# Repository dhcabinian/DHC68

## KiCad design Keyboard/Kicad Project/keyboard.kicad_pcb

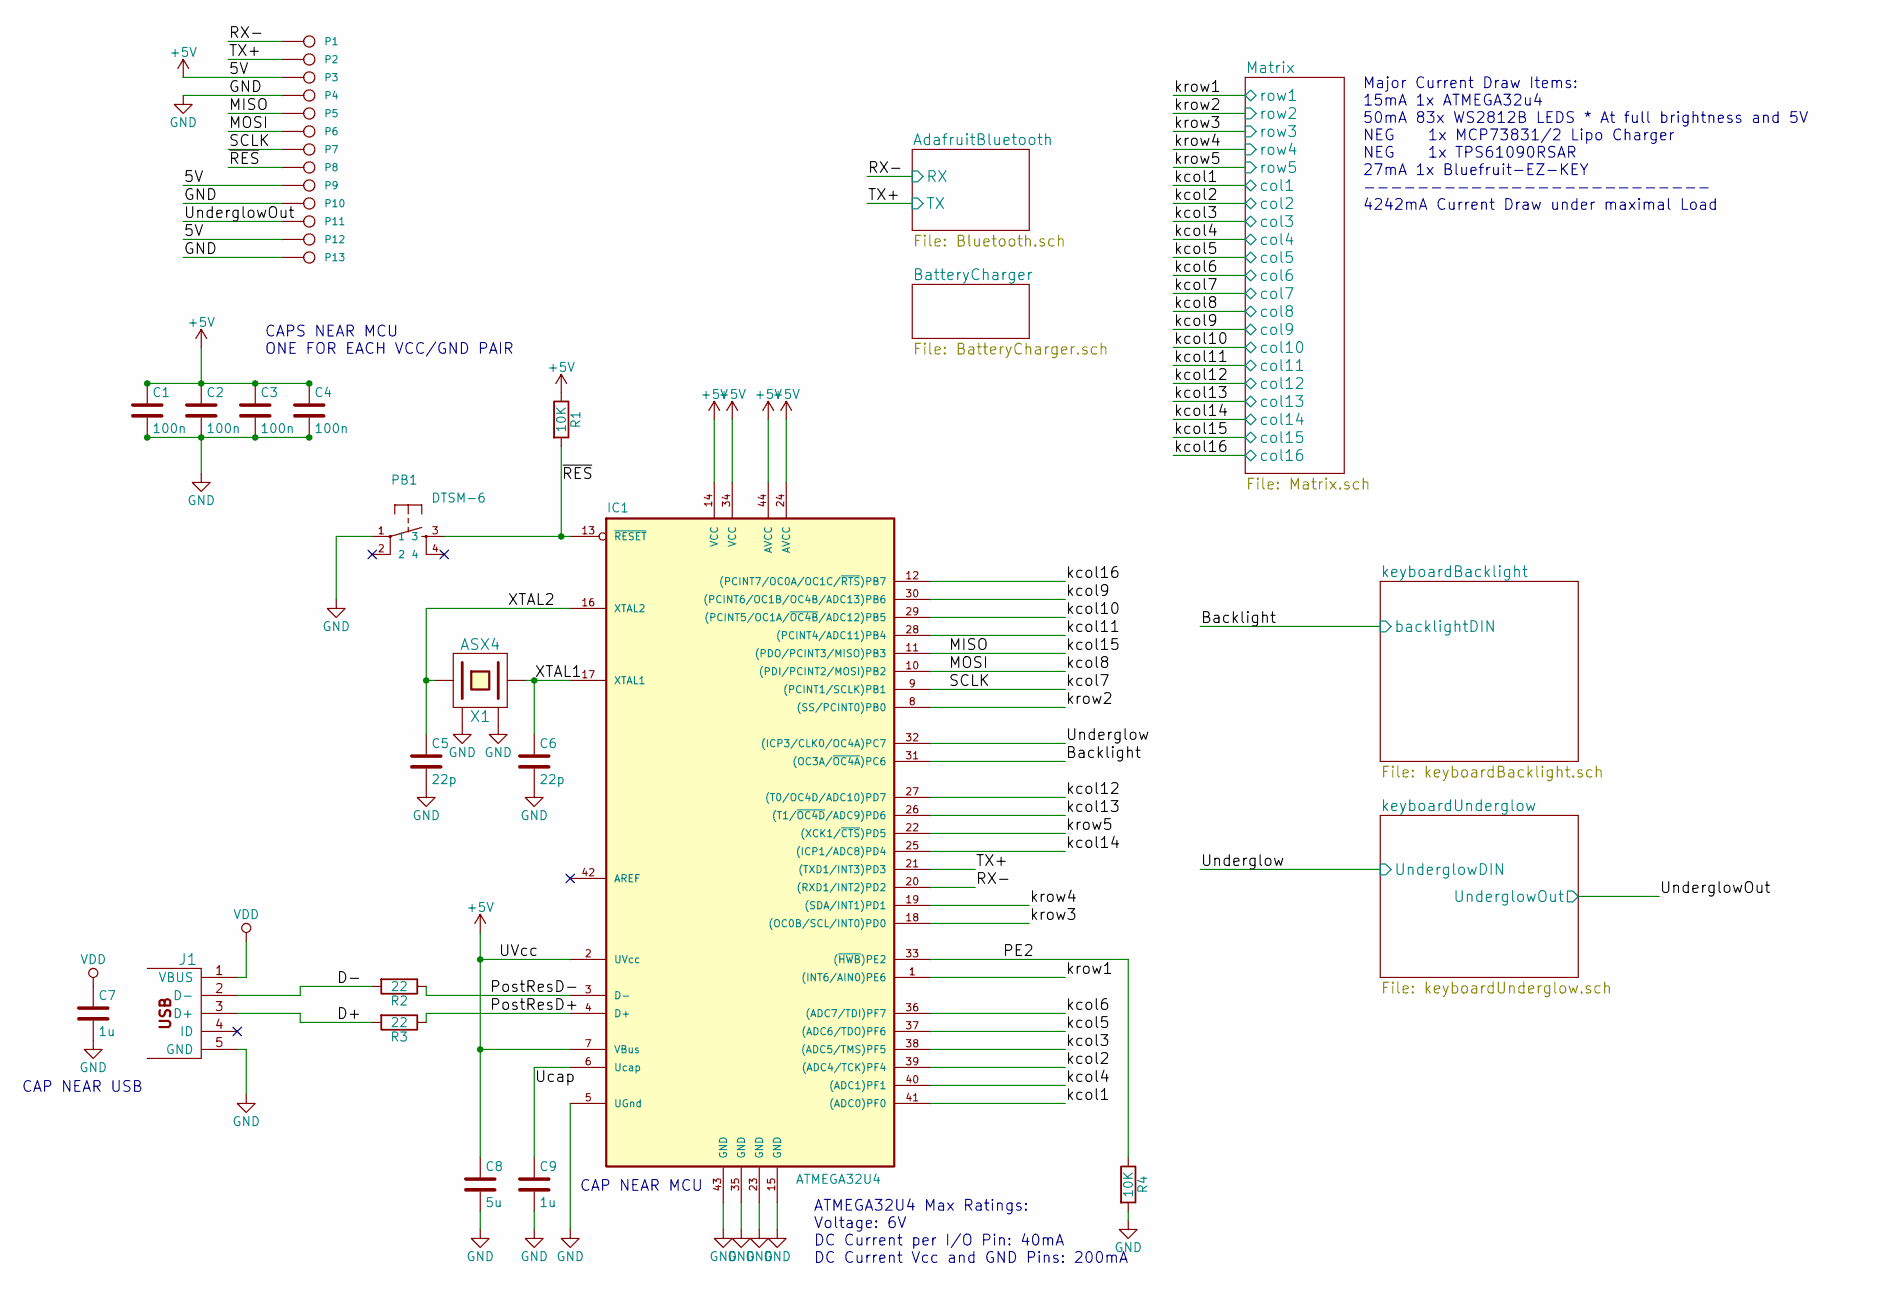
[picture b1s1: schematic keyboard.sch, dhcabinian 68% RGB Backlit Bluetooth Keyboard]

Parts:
C1, C2, C3, C4: 100n; 0805C
C5, C6: 22p; 0805C
C7, C9: 1u; 0805C
C8: 5u; 0805C
IC1: ATMEGA32U4
J1: USBMINI_B05; USBMiniB
P1, P2, P3, P4, P5, P6, P7, P8, P9, P10, P11, P12, P13: CONN_1; Throughole Connector
PB1: DTSM-6; KSEM31GLFS
R1, R4: 10K; 0805R
R2, R3: 22; 0805R
X1: ASX4; 7177M16Mhz

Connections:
+5V: C1.1, C2.1, C3.1, C4.1, C8.1, IC1.2 (UVcc), IC1.7 (VBus), IC1.14 (VCC), IC1.24 (AVCC), IC1.34 (VCC), IC1.44 (AVCC), P3.1, P9.1, P12.1, R1.1; also elsewhere on the board
/AdafruitBluetooth/RX: IC1.20 ((RXD1/INT2)PD2), P1.1; also elsewhere on the board
/AdafruitBluetooth/TX: IC1.21 ((TXD1/INT3)PD3), P2.1; also elsewhere on the board
/D+: J1.3 (D+), R3.2
/D-: J1.2 (D-), R2.2
/Matrix/col1: IC1.41 ((ADC0)PF0); also elsewhere on the board
/Matrix/col2: IC1.39 ((ADC4/TCK)PF4); also elsewhere on the board
/Matrix/col3: IC1.38 ((ADC5/TMS)PF5); also elsewhere on the board
/Matrix/col4: IC1.40 ((ADC1)PF1); also elsewhere on the board
/Matrix/col5: IC1.37 ((ADC6/TDO)PF6); also elsewhere on the board
/Matrix/col6: IC1.36 ((ADC7/TDI)PF7); also elsewhere on the board
/Matrix/col7: IC1.9 ((PCINT1/SCLK)PB1), P7.1; also elsewhere on the board
/Matrix/col8: IC1.10 ((PDI/PCINT2/MOSI)PB2), P6.1; also elsewhere on the board
/Matrix/col9: IC1.30 ((PCINT6/OC1B/OC4B/ADC13)PB6); also elsewhere on the board
/Matrix/col10: IC1.29 ((PCINT5/OC1A/~OC4B~/ADC12)PB5); also elsewhere on the board
/Matrix/col11: IC1.28 ((PCINT4/ADC11)PB4); also elsewhere on the board
/Matrix/col12: IC1.27 ((T0/OC4D/ADC10)PD7); also elsewhere on the board
/Matrix/col13: IC1.26 ((T1/~OC4D~/ADC9)PD6); also elsewhere on the board
/Matrix/col14: IC1.25 ((ICP1/ADC8)PD4); also elsewhere on the board
/Matrix/col15: IC1.11 ((PDO/PCINT3/MISO)PB3), P5.1; also elsewhere on the board
/Matrix/col16: IC1.12 ((PCINT7/OC0A/OC1C/~RTS~)PB7); also elsewhere on the board
/Matrix/row1: IC1.1 ((INT6/AIN0)PE6); also elsewhere on the board
/Matrix/row2: IC1.8 ((SS/PCINT0)PB0); also elsewhere on the board
/Matrix/row3: IC1.18 ((OC0B/SCL/INT0)PD0); also elsewhere on the board
/Matrix/row4: IC1.19 ((SDA/INT1)PD1); also elsewhere on the board
/Matrix/row5: IC1.22 ((XCK1/~CTS~)PD5); also elsewhere on the board
/PE2: IC1.33 ((~HWB~)PE2), R4.1
/PostResD+: IC1.4 (D+), R3.1
/PostResD-: IC1.3 (D-), R2.1
/Ucap: C9.1, IC1.6 (Ucap)
/XTAL1: C6.1, IC1.17 (XTAL1), X1.3 (2)
/XTAL2: C5.1, IC1.16 (XTAL2), X1.1
/keyboardBacklight/backlightDIN: IC1.31 ((OC3A/~OC4A~)PC6); also elsewhere on the board
/keyboardUnderglow/UnderglowDIN: IC1.32 ((ICP3/CLK0/OC4A)PC7); also elsewhere on the board
/keyboardUnderglow/UnderglowOut: P11.1; also elsewhere on the board
/~RES: IC1.13 (~RESET~), P8.1, PB1.3, R1.2
GND: C1.2, C2.2, C3.2, C4.2, C5.2, C6.2, C7.2, C8.2, C9.2, IC1.5 (UGnd), IC1.15 (GND), IC1.23 (GND), IC1.35 (GND), IC1.43 (GND), J1.5 (GND), P4.1, P10.1, P13.1, PB1.1, R4.2, X1.2 (GND), X1.4 (GND); also elsewhere on the board
VDD: C7.1, J1.1 (VBUS); also elsewhere on the board

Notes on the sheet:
ATMEGA32U4 Max Ratings: Voltage: 6V DC Current per I/O Pin: 40mA DC Current Vcc and GND Pins: 200mA
CAPS NEAR MCU ONE FOR EACH VCC/GND PAIR
CAP NEAR USB
CAP NEAR MCU
Major Current Draw Items: 15mA 1x ATMEGA32u4 50mA 83x WS2812B LEDS * At full brightness and 5V NEG 1x MCP73831/2 Lipo Charger NEG 1x TPS61090RSAR 27mA 1x Bluefruit-EZ-KEY -------------------------- 4242mA Current Draw under maximal Load

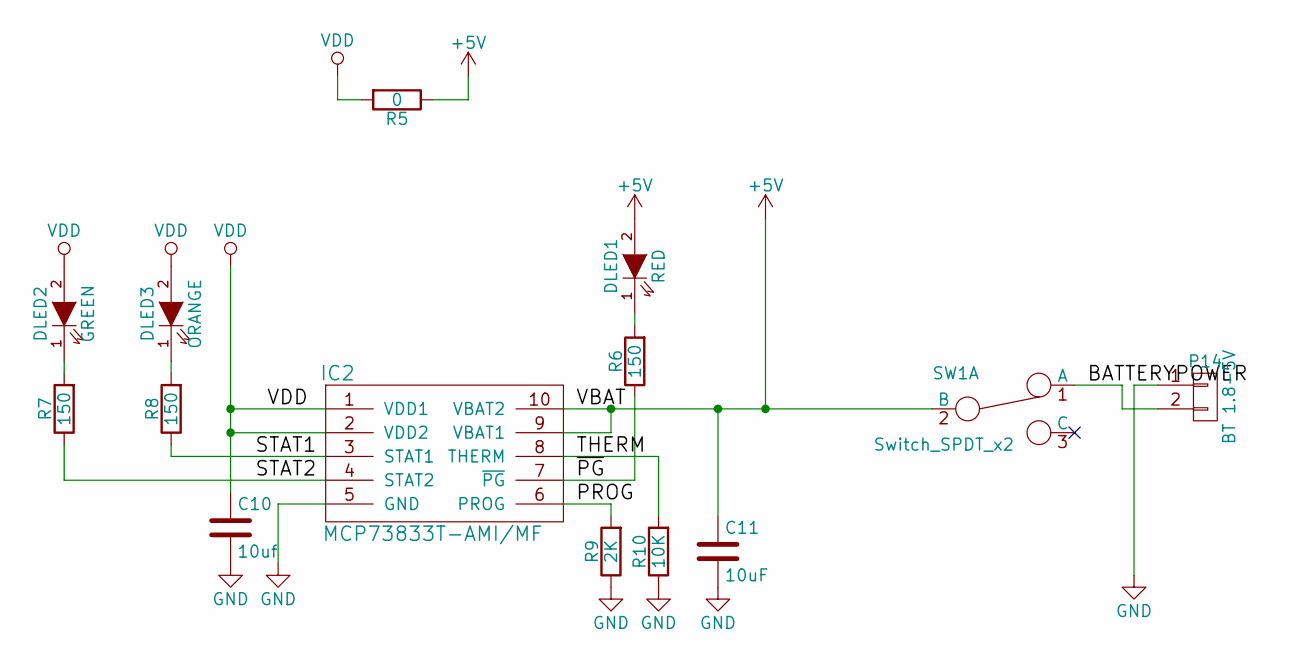
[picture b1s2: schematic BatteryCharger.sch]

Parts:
C10: 10uf; 0805C
C11: 10uF; 0805C
DLED1: RED; 0805LED
DLED2: GREEN; 0805LED
DLED3: ORANGE; 0805LED
IC2: MCP73833T-AMI/MF; MCP73833T
P14: BT 1.8-5V; JSTPH2PinConnector
R5: 0; 0805R
R6, R7, R8: 150; 0805R
R9: 2K; 0805R
R10: 10K; 0805R
SW1: Switch_SPDT_x2; CL-SA-12C4-02

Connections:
+5V: C11.1, DLED1.2 (A), IC2.9 (VBAT1), IC2.10 (VBAT2), R5.1, SW1.2 (B); also elsewhere on the board
/BatteryCharger/BATTERYPOWER: P14.2, SW1.1 (A)
/BatteryCharger/PROG: IC2.6 (PROG), R9.2
/BatteryCharger/STAT1: IC2.3 (STAT1), R8.1
/BatteryCharger/STAT2: IC2.4 (STAT2), R7.1
/BatteryCharger/THERM: IC2.8 (THERM), R10.2
/BatteryCharger/~PG: IC2.7 (~PG), R6.1
GND: C10.2, C11.2, IC2.5 (GND), P14.1, R9.1, R10.1; also elsewhere on the board
unnamed: DLED1.1 (K), R6.2
unnamed: DLED2.1 (K), R7.2
unnamed: DLED3.1 (K), R8.2
VDD: C10.1, DLED2.2 (A), DLED3.2 (A), IC2.1 (VDD1), IC2.2 (VDD2), R5.2; also elsewhere on the board

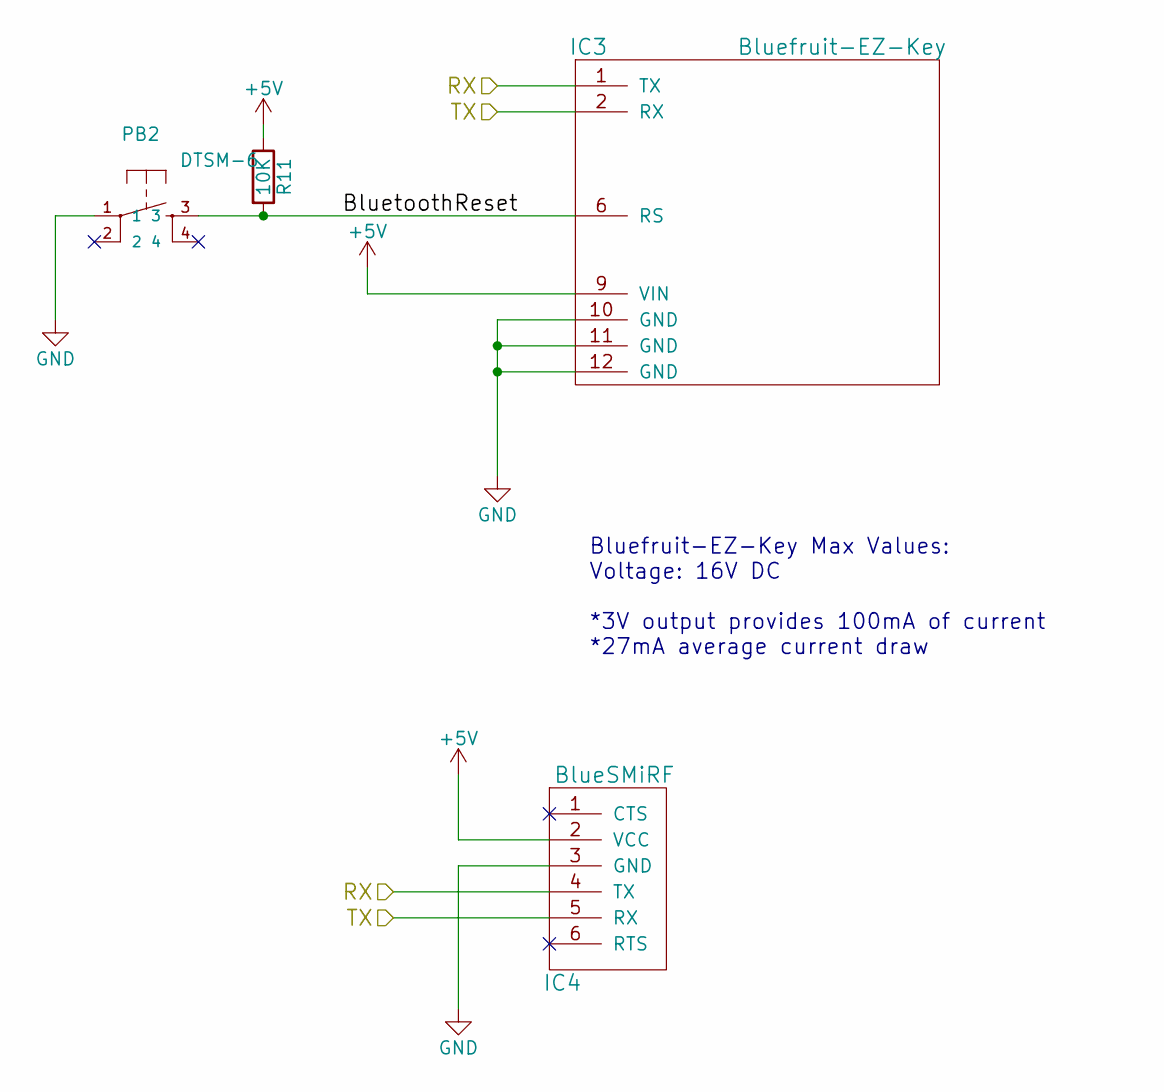
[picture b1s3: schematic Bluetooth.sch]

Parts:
IC3: Bluefruit-EZ-Key; BluefruitEzKey
IC4: BlueSMiRF
PB2: DTSM-6; KSEM31GLFS
R11: 10K; 0805R

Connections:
+5V: IC3.9 (VIN), IC4.2 (VCC), R11.1; also elsewhere on the board
/AdafruitBluetooth/BluetoothReset: IC3.6 (RS), PB2.3, R11.2
/AdafruitBluetooth/RX: IC3.1 (TX), IC4.4 (TX); also elsewhere on the board
/AdafruitBluetooth/TX: IC3.2 (RX), IC4.5 (RX); also elsewhere on the board
GND: IC3.10 (GND), IC3.11 (GND), IC3.12 (GND), IC4.3 (GND), PB2.1; also elsewhere on the board

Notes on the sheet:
Bluefruit-EZ-Key Max Values: Voltage: 16V DC *3V output provides 100mA of current *27mA average current draw

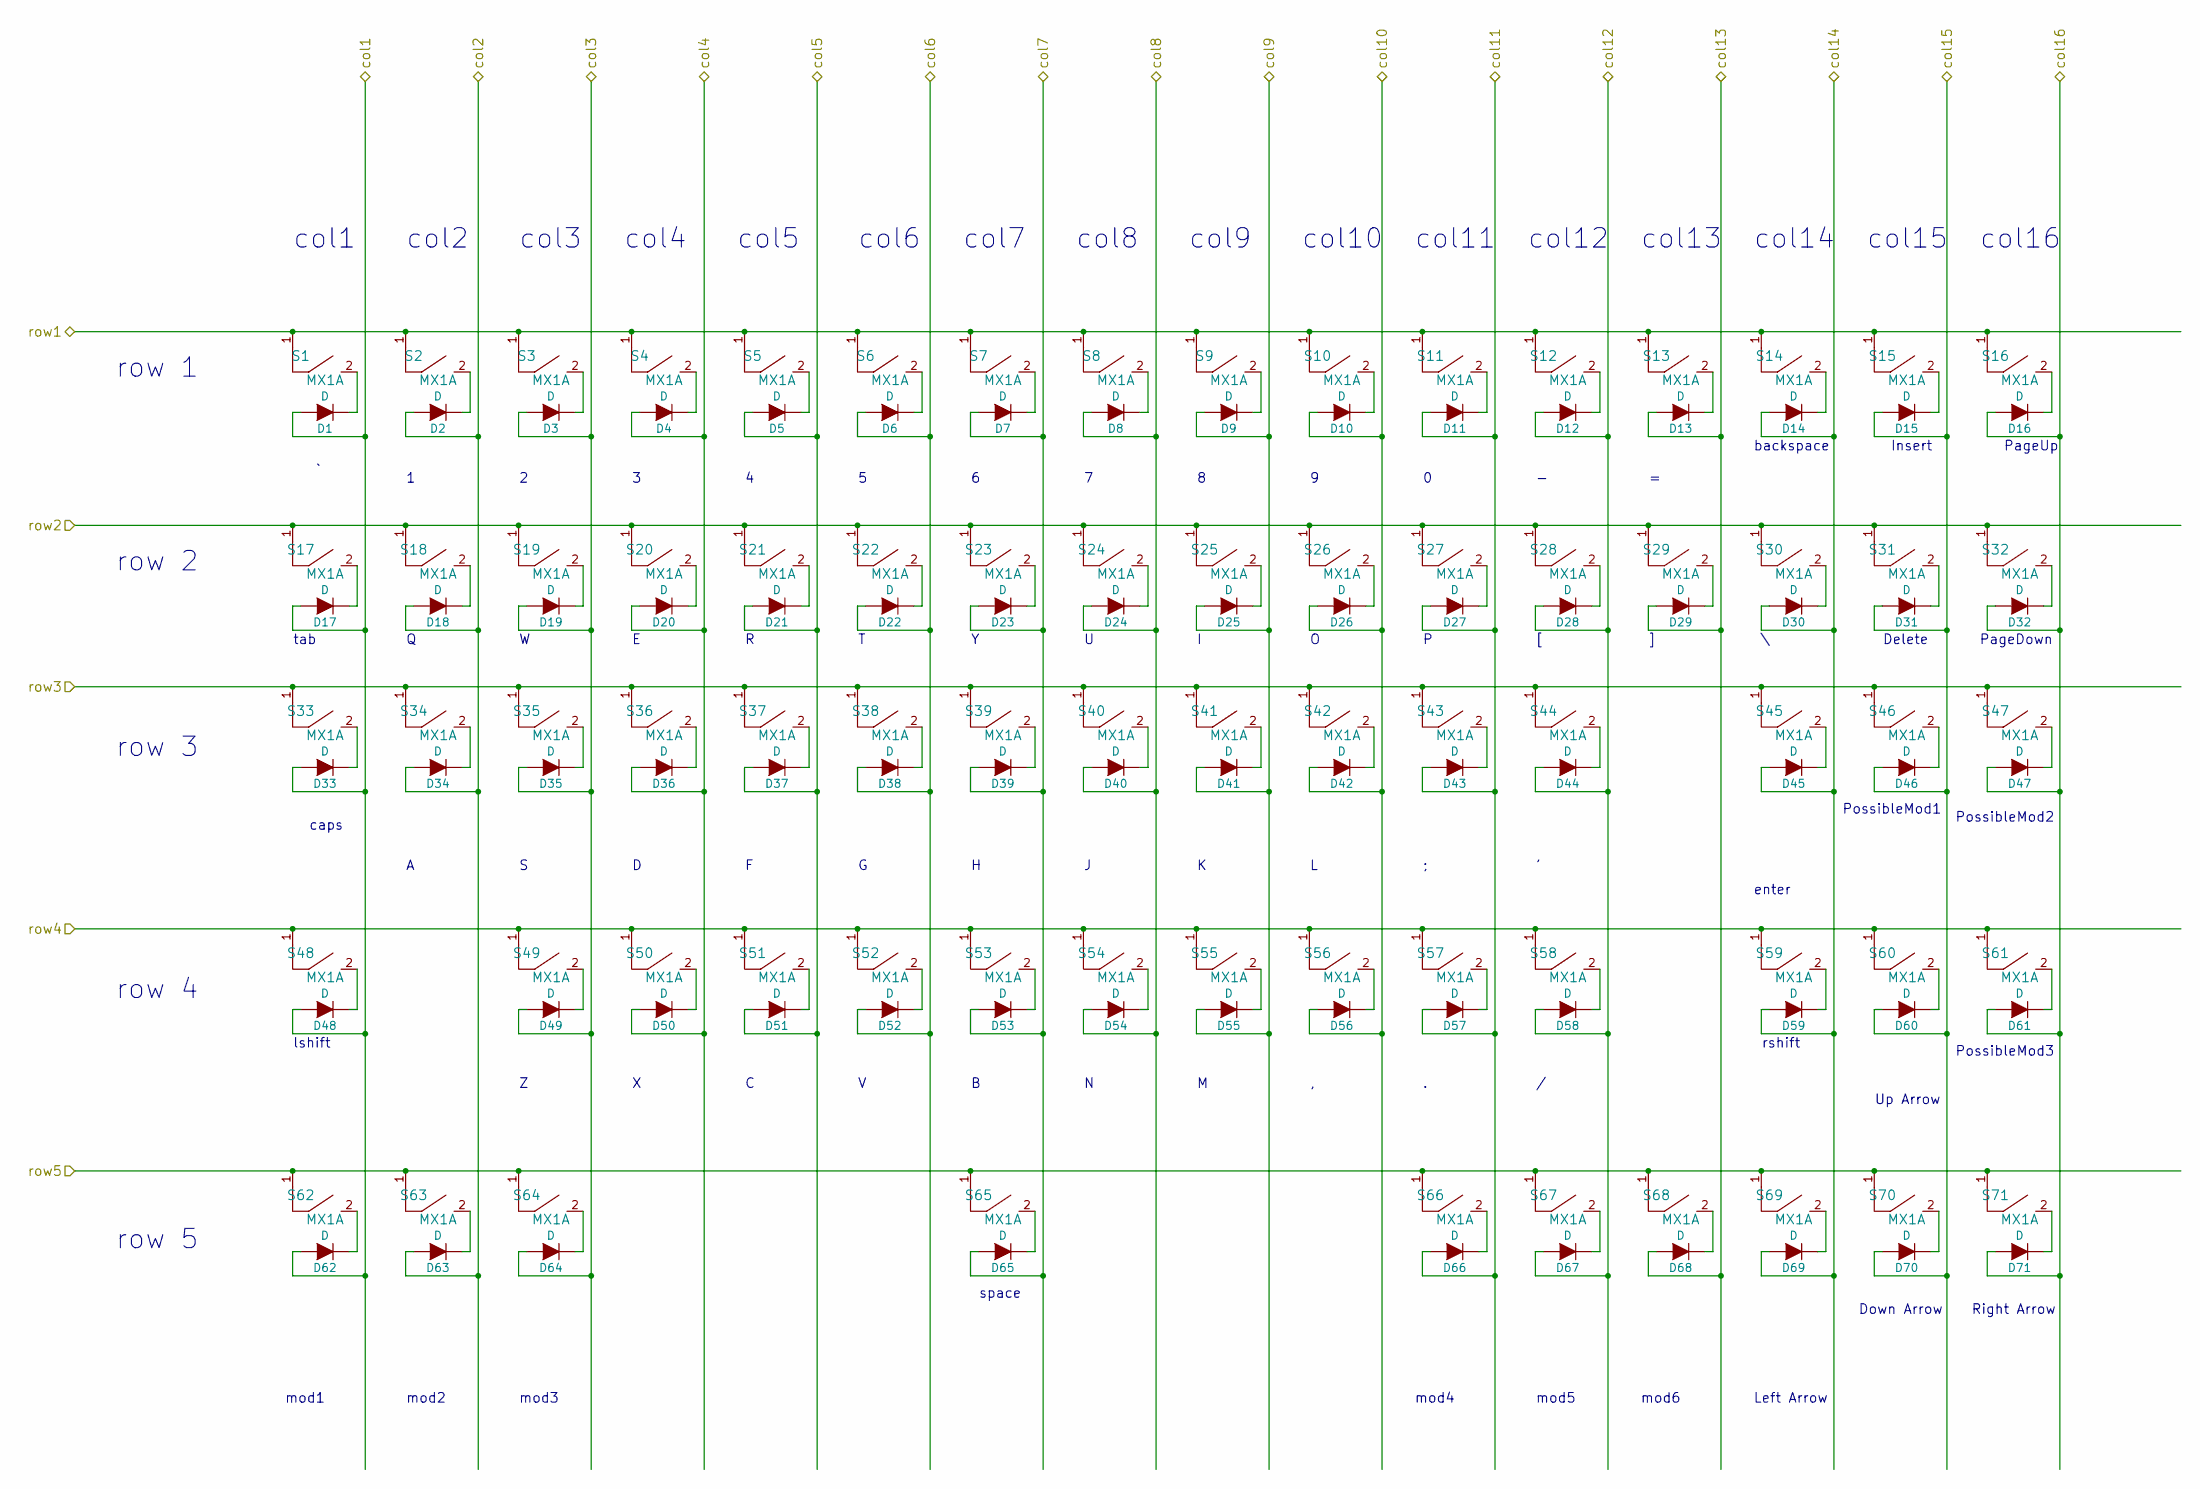
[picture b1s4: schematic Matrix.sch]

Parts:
D1, D2, D3, D4, D5, D6, D7, D8, D9, D10, D11, D12, D13, D14, D15, D16, D17, D18, D19, D20, D21, D22, D23, D24, D25, D26, D27, D28, D29, D30, D31, D32, D33, D34, D35, D36, D37, D38, D39, D40, D41, D42, D43, D44, D45, D46, D47, D48, D49, D50, D51, D52, D53, D54, D55, D56, D57, D58, D59, D60, D61, D62, D63, D64, D65, D66, D67, D68, D69, D70, D71: D; SOD-123
S1, S2, S3, S4, S5, S6, S7, S8, S9, S10, S11, S12, S13, S15, S16, S18, S19, S20, S21, S22, S23, S24, S25, S26, S27, S28, S29, S31, S32, S34, S35, S36, S37, S38, S39, S40, S41, S42, S43, S44, S46, S47, S49, S50, S51, S52, S53, S54, S55, S56, S57, S58, S60, S61, S69, S70, S71: MX1A; CHERRY_PCB_100H
S14: MX1A; CHERRY_PCB_200H
S17, S30: MX1A; CHERRY_PCB_150H
S33: MX1A; CHERRY_PCB_175H
S45, S48: MX1A; CHERRY_PCB_225H
S59: MX1A; CHERRY_PCB_275H
S62, S63, S64, S66, S67, S68: MX1A; CHERRY_PCB_125H
S65: MX1A; CHERRY_PCB_625H

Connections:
/Matrix/col1: D1.2 (A), D17.2 (A), D33.2 (A), D48.2 (A), D62.2 (A); also elsewhere on the board
/Matrix/col2: D2.2 (A), D18.2 (A), D34.2 (A), D63.2 (A); also elsewhere on the board
/Matrix/col3: D3.2 (A), D19.2 (A), D35.2 (A), D49.2 (A), D64.2 (A); also elsewhere on the board
/Matrix/col4: D4.2 (A), D20.2 (A), D36.2 (A), D50.2 (A); also elsewhere on the board
/Matrix/col5: D5.2 (A), D21.2 (A), D37.2 (A), D51.2 (A); also elsewhere on the board
/Matrix/col6: D6.2 (A), D22.2 (A), D38.2 (A), D52.2 (A); also elsewhere on the board
/Matrix/col7: D7.2 (A), D23.2 (A), D39.2 (A), D53.2 (A), D65.2 (A); also elsewhere on the board
/Matrix/col8: D8.2 (A), D24.2 (A), D40.2 (A), D54.2 (A); also elsewhere on the board
/Matrix/col9: D9.2 (A), D25.2 (A), D41.2 (A), D55.2 (A); also elsewhere on the board
/Matrix/col10: D10.2 (A), D26.2 (A), D42.2 (A), D56.2 (A); also elsewhere on the board
/Matrix/col11: D11.2 (A), D27.2 (A), D43.2 (A), D57.2 (A), D66.2 (A); also elsewhere on the board
/Matrix/col12: D12.2 (A), D28.2 (A), D44.2 (A), D58.2 (A), D67.2 (A); also elsewhere on the board
/Matrix/col13: D13.2 (A), D29.2 (A), D68.2 (A); also elsewhere on the board
/Matrix/col14: D14.2 (A), D30.2 (A), D45.2 (A), D59.2 (A), D69.2 (A); also elsewhere on the board
/Matrix/col15: D15.2 (A), D31.2 (A), D46.2 (A), D60.2 (A), D70.2 (A); also elsewhere on the board
/Matrix/col16: D16.2 (A), D32.2 (A), D47.2 (A), D61.2 (A), D71.2 (A); also elsewhere on the board
/Matrix/row1: S1.1, S2.1, S3.1, S4.1, S5.1, S6.1, S7.1, S8.1, S9.1, S10.1, S11.1, S12.1, S13.1, S14.1, S15.1, S16.1; also elsewhere on the board
/Matrix/row2: S17.1, S18.1, S19.1, S20.1, S21.1, S22.1, S23.1, S24.1, S25.1, S26.1, S27.1, S28.1, S29.1, S30.1, S31.1, S32.1; also elsewhere on the board
/Matrix/row3: S33.1, S34.1, S35.1, S36.1, S37.1, S38.1, S39.1, S40.1, S41.1, S42.1, S43.1, S44.1, S45.1, S46.1, S47.1; also elsewhere on the board
/Matrix/row4: S48.1, S49.1, S50.1, S51.1, S52.1, S53.1, S54.1, S55.1, S56.1, S57.1, S58.1, S59.1, S60.1, S61.1; also elsewhere on the board
/Matrix/row5: S62.1, S63.1, S64.1, S65.1, S66.1, S67.1, S68.1, S69.1, S70.1, S71.1; also elsewhere on the board
unnamed: D1.1 (K), S1.2
unnamed: D2.1 (K), S2.2
unnamed: D3.1 (K), S3.2
unnamed: D4.1 (K), S4.2
unnamed: D5.1 (K), S5.2
unnamed: D6.1 (K), S6.2
unnamed: D7.1 (K), S7.2
unnamed: D8.1 (K), S8.2
unnamed: D9.1 (K), S9.2
unnamed: D10.1 (K), S10.2
unnamed: D11.1 (K), S11.2
unnamed: D12.1 (K), S12.2
unnamed: D13.1 (K), S13.2
unnamed: D14.1 (K), S14.2
unnamed: D15.1 (K), S15.2
unnamed: D16.1 (K), S16.2
unnamed: D17.1 (K), S17.2
unnamed: D18.1 (K), S18.2
unnamed: D19.1 (K), S19.2
unnamed: D20.1 (K), S20.2
unnamed: D21.1 (K), S21.2
unnamed: D22.1 (K), S22.2
unnamed: D23.1 (K), S23.2
unnamed: D24.1 (K), S24.2
unnamed: D25.1 (K), S25.2
unnamed: D26.1 (K), S26.2
unnamed: D27.1 (K), S27.2
unnamed: D28.1 (K), S28.2
unnamed: D29.1 (K), S29.2
unnamed: D30.1 (K), S30.2
unnamed: D31.1 (K), S31.2
unnamed: D32.1 (K), S32.2
unnamed: D33.1 (K), S33.2
unnamed: D34.1 (K), S34.2
unnamed: D35.1 (K), S35.2
unnamed: D36.1 (K), S36.2
unnamed: D37.1 (K), S37.2
unnamed: D38.1 (K), S38.2
unnamed: D39.1 (K), S39.2
unnamed: D40.1 (K), S40.2
unnamed: D41.1 (K), S41.2
unnamed: D42.1 (K), S42.2
unnamed: D43.1 (K), S43.2
unnamed: D44.1 (K), S44.2
unnamed: D45.1 (K), S45.2
unnamed: D46.1 (K), S46.2
unnamed: D47.1 (K), S47.2
unnamed: D48.1 (K), S48.2
unnamed: D49.1 (K), S49.2
unnamed: D50.1 (K), S50.2
unnamed: D51.1 (K), S51.2
unnamed: D52.1 (K), S52.2
unnamed: D53.1 (K), S53.2
unnamed: D54.1 (K), S54.2
unnamed: D55.1 (K), S55.2
unnamed: D56.1 (K), S56.2
unnamed: D57.1 (K), S57.2
unnamed: D58.1 (K), S58.2
unnamed: D59.1 (K), S59.2
unnamed: D60.1 (K), S60.2
unnamed: D61.1 (K), S61.2
unnamed: D62.1 (K), S62.2
unnamed: D63.1 (K), S63.2
unnamed: D64.1 (K), S64.2
unnamed: D65.1 (K), S65.2
unnamed: D66.1 (K), S66.2
unnamed: D67.1 (K), S67.2
unnamed: D68.1 (K), S68.2
unnamed: D69.1 (K), S69.2
unnamed: D70.1 (K), S70.2
unnamed: D71.1 (K), S71.2

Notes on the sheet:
row 1
row 2
row 3
row 4
row 5
col1
col2
col3
col4
col5
col6
col7
col9
col10
col11
col12
col13
col14
col8
~ `
backspace
tab
caps
enter
lshift
rshift
mod1
mod2
mod3
space
mod4
mod5
mod6
Left Arrow
col15
col16
Up Arrow
Down Arrow
Right Arrow
Insert

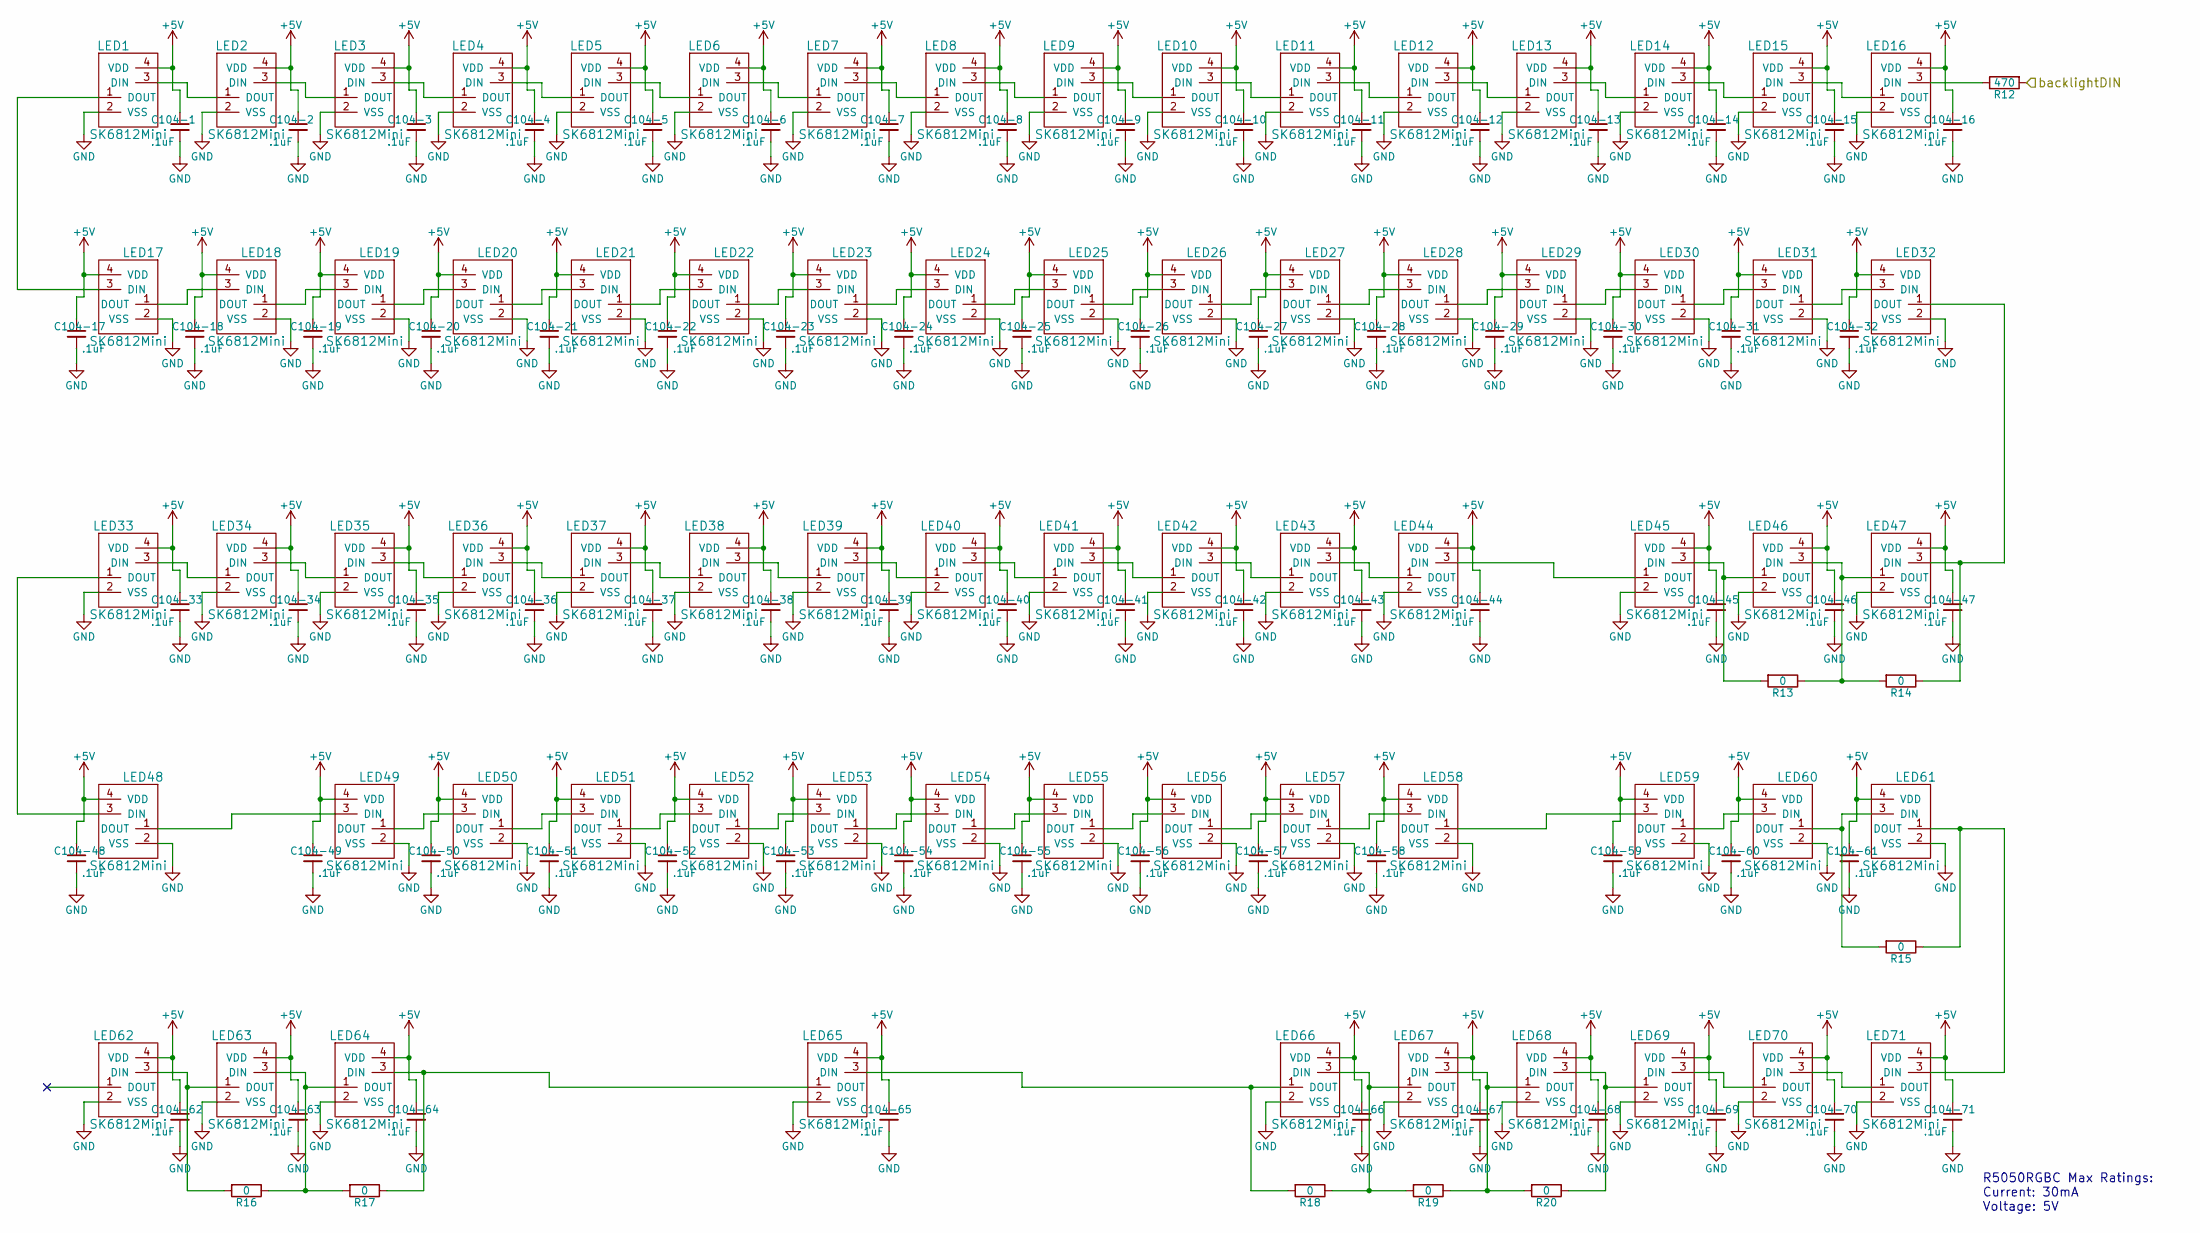
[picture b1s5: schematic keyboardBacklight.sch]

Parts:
C104-1, C104-2, C104-3, C104-4, C104-5, C104-6, C104-7, C104-8, C104-9, C104-10, C104-11, C104-12, C104-13, C104-14, C104-15, C104-16, C104-17, C104-18, C104-19, C104-20, C104-21, C104-22, C104-23, C104-24, C104-25, C104-26, C104-27, C104-28, C104-29, C104-30, C104-31, C104-32, C104-33, C104-34, C104-35, C104-36, C104-37, C104-38, C104-39, C104-40, C104-41, C104-42, C104-43, C104-44, C104-45, C104-46, C104-47, C104-48, C104-49, C104-50, C104-51, C104-52, C104-53, C104-54, C104-55, C104-56, C104-57, C104-58, C104-59, C104-60, C104-61, C104-62, C104-63, C104-64, C104-65, C104-66, C104-67, C104-68, C104-69, C104-70, C104-71: .1uF; 0805C
LED1, LED2, LED3, LED4, LED5, LED6, LED7, LED8, LED9, LED10, LED11, LED12, LED13, LED14, LED15, LED16, LED17, LED18, LED19, LED20, LED21, LED22, LED23, LED24, LED25, LED26, LED27, LED28, LED29, LED30, LED31, LED32, LED33, LED34, LED35, LED36, LED37, LED38, LED39, LED40, LED41, LED42, LED43, LED44, LED45, LED46, LED47, LED48, LED49, LED50, LED51, LED52, LED53, LED54, LED55, LED56, LED57, LED58, LED59, LED60, LED61, LED62, LED63, LED64, LED65, LED66, LED67, LED68, LED69, LED70, LED71: SK6812Mini; Sk6812Mini
R12: 470; 0805R
R13, R14, R15, R16, R17, R18, R19, R20: 0; 0805R

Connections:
+5V: C104-1.1, C104-2.1, C104-3.1, C104-4.1, C104-5.1, C104-6.1, C104-7.1, C104-8.1, C104-9.1, C104-10.1, C104-11.1, C104-12.1, C104-13.1, C104-14.1, C104-15.1, C104-16.1, C104-17.1, C104-18.1, C104-19.1, C104-20.1, C104-21.1, C104-22.1, C104-23.1, C104-24.1, C104-25.1, C104-26.1, C104-27.1, C104-28.1, C104-29.1, C104-30.1, C104-31.1, C104-32.1, C104-33.1, C104-34.1, C104-35.1, C104-36.1, C104-37.1, C104-38.1, C104-39.1, C104-40.1, C104-41.1, C104-42.1, C104-43.1, C104-44.1, C104-45.1, C104-46.1, C104-47.1, C104-48.1, C104-49.1, C104-50.1, C104-51.1, C104-52.1, C104-53.1, C104-54.1, C104-55.1, C104-56.1, C104-57.1, C104-58.1, C104-59.1, C104-60.1, C104-61.1, C104-62.1, C104-63.1, C104-64.1, C104-65.1, C104-66.1, C104-67.1, C104-68.1, C104-69.1, C104-70.1, C104-71.1, LED1.4 (VDD), LED2.4 (VDD), LED3.4 (VDD), LED4.4 (VDD), LED5.4 (VDD), LED6.4 (VDD), LED7.4 (VDD), LED8.4 (VDD), LED9.4 (VDD), LED10.4 (VDD), LED11.4 (VDD), LED12.4 (VDD), LED13.4 (VDD), LED14.4 (VDD), LED15.4 (VDD), LED16.4 (VDD), LED17.4 (VDD), LED18.4 (VDD), LED19.4 (VDD), LED20.4 (VDD), LED21.4 (VDD), LED22.4 (VDD), LED23.4 (VDD), LED24.4 (VDD), LED25.4 (VDD), LED26.4 (VDD), LED27.4 (VDD), LED28.4 (VDD), LED29.4 (VDD), LED30.4 (VDD), LED31.4 (VDD), LED32.4 (VDD), LED33.4 (VDD), LED34.4 (VDD), LED35.4 (VDD), LED36.4 (VDD), LED37.4 (VDD), LED38.4 (VDD), LED39.4 (VDD), LED40.4 (VDD), LED41.4 (VDD), LED42.4 (VDD), LED43.4 (VDD), LED44.4 (VDD), LED45.4 (VDD), LED46.4 (VDD), LED47.4 (VDD), LED48.4 (VDD), LED49.4 (VDD), LED50.4 (VDD), LED51.4 (VDD), LED52.4 (VDD), LED53.4 (VDD), LED54.4 (VDD), LED55.4 (VDD), LED56.4 (VDD), LED57.4 (VDD), LED58.4 (VDD), LED59.4 (VDD), LED60.4 (VDD), LED61.4 (VDD), LED62.4 (VDD), LED63.4 (VDD), LED64.4 (VDD), LED65.4 (VDD), LED66.4 (VDD), LED67.4 (VDD), LED68.4 (VDD), LED69.4 (VDD), LED70.4 (VDD), LED71.4 (VDD); also elsewhere on the board
/keyboardBacklight/backlightDIN: R12.2; also elsewhere on the board
GND: C104-1.2, C104-2.2, C104-3.2, C104-4.2, C104-5.2, C104-6.2, C104-7.2, C104-8.2, C104-9.2, C104-10.2, C104-11.2, C104-12.2, C104-13.2, C104-14.2, C104-15.2, C104-16.2, C104-17.2, C104-18.2, C104-19.2, C104-20.2, C104-21.2, C104-22.2, C104-23.2, C104-24.2, C104-25.2, C104-26.2, C104-27.2, C104-28.2, C104-29.2, C104-30.2, C104-31.2, C104-32.2, C104-33.2, C104-34.2, C104-35.2, C104-36.2, C104-37.2, C104-38.2, C104-39.2, C104-40.2, C104-41.2, C104-42.2, C104-43.2, C104-44.2, C104-45.2, C104-46.2, C104-47.2, C104-48.2, C104-49.2, C104-50.2, C104-51.2, C104-52.2, C104-53.2, C104-54.2, C104-55.2, C104-56.2, C104-57.2, C104-58.2, C104-59.2, C104-60.2, C104-61.2, C104-62.2, C104-63.2, C104-64.2, C104-65.2, C104-66.2, C104-67.2, C104-68.2, C104-69.2, C104-70.2, C104-71.2, LED1.2 (VSS), LED2.2 (VSS), LED3.2 (VSS), LED4.2 (VSS), LED5.2 (VSS), LED6.2 (VSS), LED7.2 (VSS), LED8.2 (VSS), LED9.2 (VSS), LED10.2 (VSS), LED11.2 (VSS), LED12.2 (VSS), LED13.2 (VSS), LED14.2 (VSS), LED15.2 (VSS), LED16.2 (VSS), LED17.2 (VSS), LED18.2 (VSS), LED19.2 (VSS), LED20.2 (VSS), LED21.2 (VSS), LED22.2 (VSS), LED23.2 (VSS), LED24.2 (VSS), LED25.2 (VSS), LED26.2 (VSS), LED27.2 (VSS), LED28.2 (VSS), LED29.2 (VSS), LED30.2 (VSS), LED31.2 (VSS), LED32.2 (VSS), LED33.2 (VSS), LED34.2 (VSS), LED35.2 (VSS), LED36.2 (VSS), LED37.2 (VSS), LED38.2 (VSS), LED39.2 (VSS), LED40.2 (VSS), LED41.2 (VSS), LED42.2 (VSS), LED43.2 (VSS), LED44.2 (VSS), LED45.2 (VSS), LED46.2 (VSS), LED47.2 (VSS), LED48.2 (VSS), LED49.2 (VSS), LED50.2 (VSS), LED51.2 (VSS), LED52.2 (VSS), LED53.2 (VSS), LED54.2 (VSS), LED55.2 (VSS), LED56.2 (VSS), LED57.2 (VSS), LED58.2 (VSS), LED59.2 (VSS), LED60.2 (VSS), LED61.2 (VSS), LED62.2 (VSS), LED63.2 (VSS), LED64.2 (VSS), LED65.2 (VSS), LED66.2 (VSS), LED67.2 (VSS), LED68.2 (VSS), LED69.2 (VSS), LED70.2 (VSS), LED71.2 (VSS); also elsewhere on the board
unnamed: LED1.1 (DOUT), LED17.3 (DIN)
unnamed: LED1.3 (DIN), LED2.1 (DOUT)
unnamed: LED2.3 (DIN), LED3.1 (DOUT)
unnamed: LED3.3 (DIN), LED4.1 (DOUT)
unnamed: LED4.3 (DIN), LED5.1 (DOUT)
unnamed: LED5.3 (DIN), LED6.1 (DOUT)
unnamed: LED6.3 (DIN), LED7.1 (DOUT)
unnamed: LED7.3 (DIN), LED8.1 (DOUT)
unnamed: LED8.3 (DIN), LED9.1 (DOUT)
unnamed: LED9.3 (DIN), LED10.1 (DOUT)
unnamed: LED10.3 (DIN), LED11.1 (DOUT)
unnamed: LED11.3 (DIN), LED12.1 (DOUT)
unnamed: LED12.3 (DIN), LED13.1 (DOUT)
unnamed: LED13.3 (DIN), LED14.1 (DOUT)
unnamed: LED14.3 (DIN), LED15.1 (DOUT)
unnamed: LED15.3 (DIN), LED16.1 (DOUT)
unnamed: LED16.3 (DIN), R12.1
unnamed: LED17.1 (DOUT), LED18.3 (DIN)
unnamed: LED18.1 (DOUT), LED19.3 (DIN)
unnamed: LED19.1 (DOUT), LED20.3 (DIN)
unnamed: LED20.1 (DOUT), LED21.3 (DIN)
unnamed: LED21.1 (DOUT), LED22.3 (DIN)
unnamed: LED22.1 (DOUT), LED23.3 (DIN)
unnamed: LED23.1 (DOUT), LED24.3 (DIN)
unnamed: LED24.1 (DOUT), LED25.3 (DIN)
unnamed: LED25.1 (DOUT), LED26.3 (DIN)
unnamed: LED26.1 (DOUT), LED27.3 (DIN)
unnamed: LED27.1 (DOUT), LED28.3 (DIN)
unnamed: LED28.1 (DOUT), LED29.3 (DIN)
unnamed: LED29.1 (DOUT), LED30.3 (DIN)
unnamed: LED30.1 (DOUT), LED31.3 (DIN)
unnamed: LED31.1 (DOUT), LED32.3 (DIN)
unnamed: LED32.1 (DOUT), LED47.3 (DIN), R14.1
unnamed: LED33.1 (DOUT), LED48.3 (DIN)
unnamed: LED33.3 (DIN), LED34.1 (DOUT)
unnamed: LED34.3 (DIN), LED35.1 (DOUT)
unnamed: LED35.3 (DIN), LED36.1 (DOUT)
unnamed: LED36.3 (DIN), LED37.1 (DOUT)
unnamed: LED37.3 (DIN), LED38.1 (DOUT)
unnamed: LED38.3 (DIN), LED39.1 (DOUT)
unnamed: LED39.3 (DIN), LED40.1 (DOUT)
unnamed: LED40.3 (DIN), LED41.1 (DOUT)
unnamed: LED41.3 (DIN), LED42.1 (DOUT)
unnamed: LED42.3 (DIN), LED43.1 (DOUT)
unnamed: LED43.3 (DIN), LED44.1 (DOUT)
unnamed: LED44.3 (DIN), LED45.1 (DOUT)
unnamed: LED45.3 (DIN), LED46.1 (DOUT), R13.2
unnamed: LED46.3 (DIN), LED47.1 (DOUT), R13.1, R14.2
unnamed: LED48.1 (DOUT), LED49.3 (DIN)
unnamed: LED49.1 (DOUT), LED50.3 (DIN)
unnamed: LED50.1 (DOUT), LED51.3 (DIN)
unnamed: LED51.1 (DOUT), LED52.3 (DIN)
unnamed: LED52.1 (DOUT), LED53.3 (DIN)
unnamed: LED53.1 (DOUT), LED54.3 (DIN)
unnamed: LED54.1 (DOUT), LED55.3 (DIN)
unnamed: LED55.1 (DOUT), LED56.3 (DIN)
unnamed: LED56.1 (DOUT), LED57.3 (DIN)
unnamed: LED57.1 (DOUT), LED58.3 (DIN)
unnamed: LED58.1 (DOUT), LED59.3 (DIN)
unnamed: LED59.1 (DOUT), LED60.3 (DIN)
unnamed: LED60.1 (DOUT), LED61.3 (DIN), R15.2
unnamed: LED61.1 (DOUT), LED71.3 (DIN), R15.1
unnamed: LED62.3 (DIN), LED63.1 (DOUT), R16.2
unnamed: LED63.3 (DIN), LED64.1 (DOUT), R16.1, R17.2
unnamed: LED64.3 (DIN), LED65.1 (DOUT), R17.1
unnamed: LED65.3 (DIN), LED66.1 (DOUT), R18.2
unnamed: LED66.3 (DIN), LED67.1 (DOUT), R18.1, R19.2
unnamed: LED67.3 (DIN), LED68.1 (DOUT), R19.1, R20.2
unnamed: LED68.3 (DIN), LED69.1 (DOUT), R20.1
unnamed: LED69.3 (DIN), LED70.1 (DOUT)
unnamed: LED70.3 (DIN), LED71.1 (DOUT)

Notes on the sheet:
R5050RGBC Max Ratings: Current: 30mA Voltage: 5V
